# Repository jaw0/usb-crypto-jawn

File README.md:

Hardware encryption, sd card, and usb port.

The current firmware implements an encrypted
"usb stick".

Like [Bitlocker](http://css.csail.mit.edu/6.858/2013/readings/bitlocker.pdf),
but with the addition of per disk-block IVs + MACs.

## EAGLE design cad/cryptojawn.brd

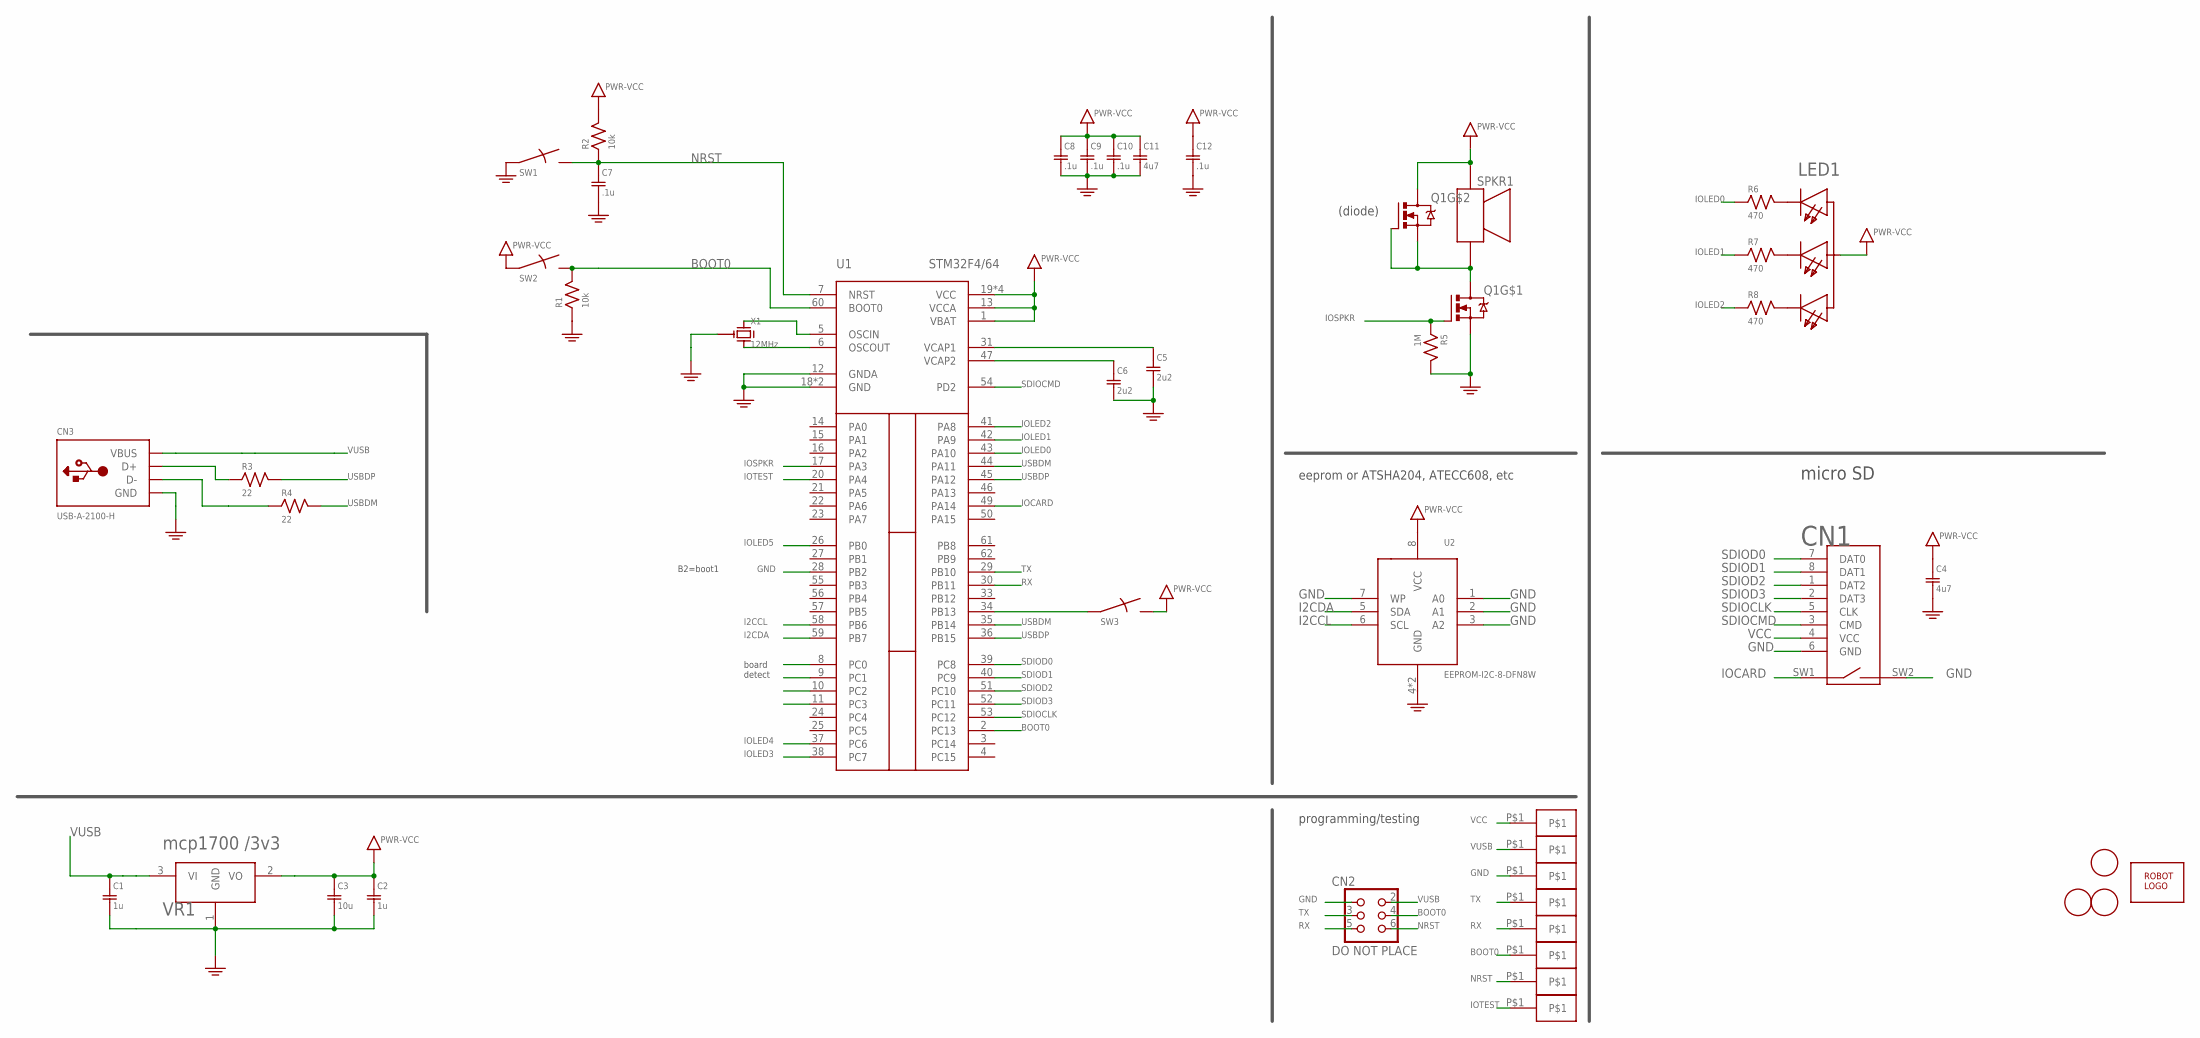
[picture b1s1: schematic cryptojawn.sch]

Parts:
C1, C2: 1u; SMD0603
C3: 10u; SMD0603
C4, C11: 4u7; SMD0603
C5, C6: 2u2; SMD0603
C7, C8, C9, C10, C12: .1u; SMD0603
CN1: MICROSDPLAIN; MICROSD/MOLEX/FRONT/PLAIN
CN2: DO NOT PLACE; HEADER-3X2-PTH1.27
CN3: USB-A-2100-H; MOLEX_480372100-HOLE
CN4, CN5, CN6, CN7, CN8, CN9, CN10, CN11: HEADER-1X1-SPOT; SPOT
LED1: LED-RGB-CA-PLCC4; PLCC4-3228
Q1: DMN63D8LDW; SC-70-6
R1, R2: 10k; SMD0603
R3, R4: 22; SMD0603
R5: 1M; SMD0603
R6, R7, R8: 470; SMD0603
SPKR1: SPKR-PUI-0440; PUI-0440
SW1, SW2, SW3: SWITCH-PTS810; PTS810
U1: STM32F4/64; TQFP64
U2: EEPROM-I2C-8-DFN8W; TDFN8EPW
U$1: ROBOTMAN-LOGO
U$2, U$3, U$4: FIDUCIAL; FIDUCIAL_1MM
VR1: mcp1700 /3v3; SOT-23-3@1
X1: 12MHz; RESONATOR-CSTCE

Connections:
BOOT0: CN2.4, CN8.P$1, R1.2, SW2.P$2, SW2.P$2B, U1.2 (PC13), U1.60 (BOOT0)
GND: C1.2, C2.2, C3.2, C4.2, C5.2, C6.2, C7.2, C8.2, C9.2, C10.2, C11.2, C12.2, CN1.6 (GND), CN1.SW2, CN2.1, CN3.4 (GND), CN3.P$1 (GND), CN3.P$2 (GND), CN5.P$1, Q1.1 (S), R1.1, R5.2, SW1.P$1, SW1.P$1B, U1.12 (GNDA), U1.18 (GND), U1.28 (PB2), U1.63 (GND), U2.1 (A0), U2.2 (A1), U2.3 (A2), U2.4 (GND), U2.7 (WP), U2.PAD (GND), VR1.1 (GND), X1.2 (G)
I2CCL: U1.58 (PB6), U2.6 (SCL)
I2CDA: U1.59 (PB7), U2.5 (SDA)
IOCARD: CN1.SW1, U1.49 (PA14)
IOLED0: R6.1, U1.43 (PA10)
IOLED1: R7.1, U1.42 (PA9)
IOLED2: R8.1, U1.41 (PA8)
IOLED3: U1.38 (PC7)
IOLED4: U1.37 (PC6)
IOLED5: U1.26 (PB0)
IOSPKR: Q1.2 (G), R5.1, U1.17 (PA3)
IOTEST: CN11.P$1, U1.20 (PA4)
unnamed: LED1.P$4 (CB), R7.2
unnamed: SW3.P$1, SW3.P$1B, U1.34 (PB13)
unnamed: LED1.P$2 (CR), R8.2
unnamed: C6.1, U1.47 (VCAP2)
unnamed: LED1.P$3 (CG), R6.2
unnamed: CN3.2 (D-), R4.1
unnamed: CN3.3 (D+), R3.1
unnamed: U1.5 (OSCIN), X1.1 (X1)
unnamed: U1.6 (OSCOUT), X1.3 (X2)
unnamed: Q1.4 (S), Q1.5 (G), Q1.6 (D), SPKR1.P$2 (P2)
unnamed: C5.1, U1.31 (VCAP1)
NRST: C7.1, CN2.6, CN9.P$1, R2.1, SW1.P$2, SW1.P$2B, U1.7 (NRST)
RX: CN2.5, CN7.P$1, U1.30 (PB11)
SDIOCLK: CN1.5 (CLK), U1.53 (PC12)
SDIOCMD: CN1.3 (CMD), U1.54 (PD2)
SDIOD0: CN1.7 (DAT0), U1.39 (PC8)
SDIOD1: CN1.8 (DAT1), U1.40 (PC9)
SDIOD2: CN1.1 (DAT2), U1.51 (PC10)
SDIOD3: CN1.2 (DAT3), U1.52 (PC11)
TX: CN2.3, CN6.P$1, U1.29 (PB10)
USBDM: R4.2, U1.35 (PB14), U1.44 (PA11)
USBDP: R3.2, U1.36 (PB15), U1.45 (PA12)
VCC: C2.1, C3.1, C4.1, C8.1, C9.1, C10.1, C11.1, C12.1, CN1.4 (VCC), CN10.P$1, LED1.P$1 (A), Q1.3 (D), R2.2, SPKR1.P$1 (P1), SW2.P$1, SW2.P$1B, SW3.P$2, SW3.P$2B, U1.1 (VBAT), U1.13 (VCCA), U1.19 (VCC), U1.32 (VCC), U1.48 (VCC), U1.64 (VCC), U2.8 (VCC), VR1.2 (VO)
VUSB: C1.1, CN2.2, CN3.1 (VBUS), CN4.P$1, VR1.3 (VI)

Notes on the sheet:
micro SD
eeprom or ATSHA204, ATECC608, etc
programming/testing
(diode)
B2=boot1
board detect

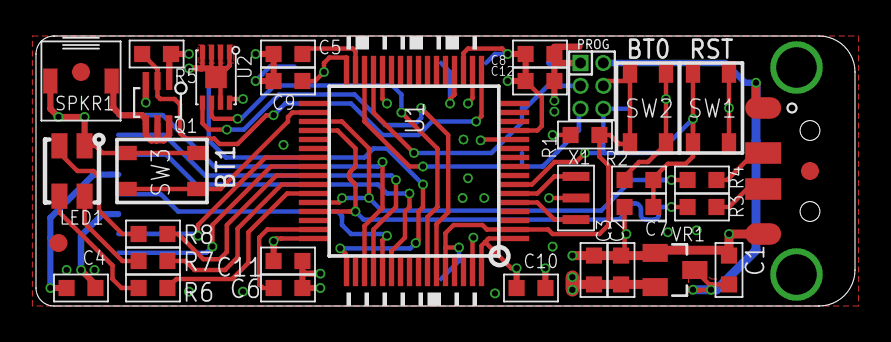
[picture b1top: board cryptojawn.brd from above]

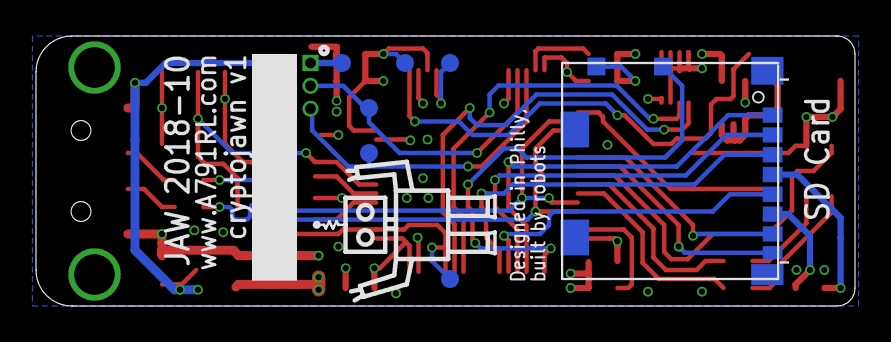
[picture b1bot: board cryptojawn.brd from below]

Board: 4 copper layers, 45.5 x 15.0 mm, 45 parts (10 on the bottom side), 34 nets.

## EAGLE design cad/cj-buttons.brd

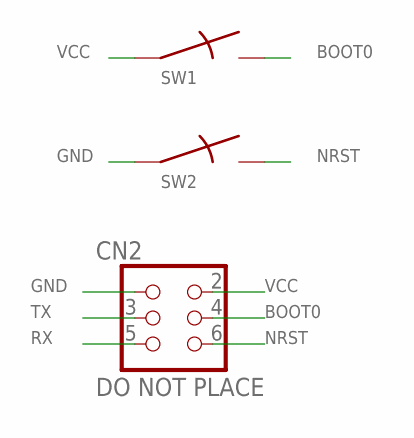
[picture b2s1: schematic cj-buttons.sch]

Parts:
CN2: DO NOT PLACE; HEADER-3X2-PTH1.27
SW1, SW2: SWITCHKMR211; KMR211

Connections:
BOOT0: CN2.4, SW1.2, SW1.4
GND: CN2.1, SW2.1, SW2.3
NRST: CN2.6, SW2.2, SW2.4
RX: CN2.5
TX: CN2.3
VCC: CN2.2, SW1.1, SW1.3

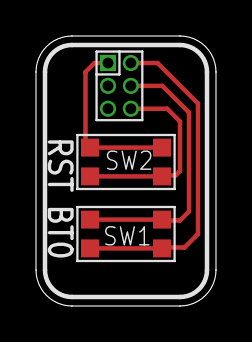
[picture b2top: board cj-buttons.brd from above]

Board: 2 copper layers, 10.0 x 15.0 mm, 3 parts (0 on the bottom side), 4 nets.

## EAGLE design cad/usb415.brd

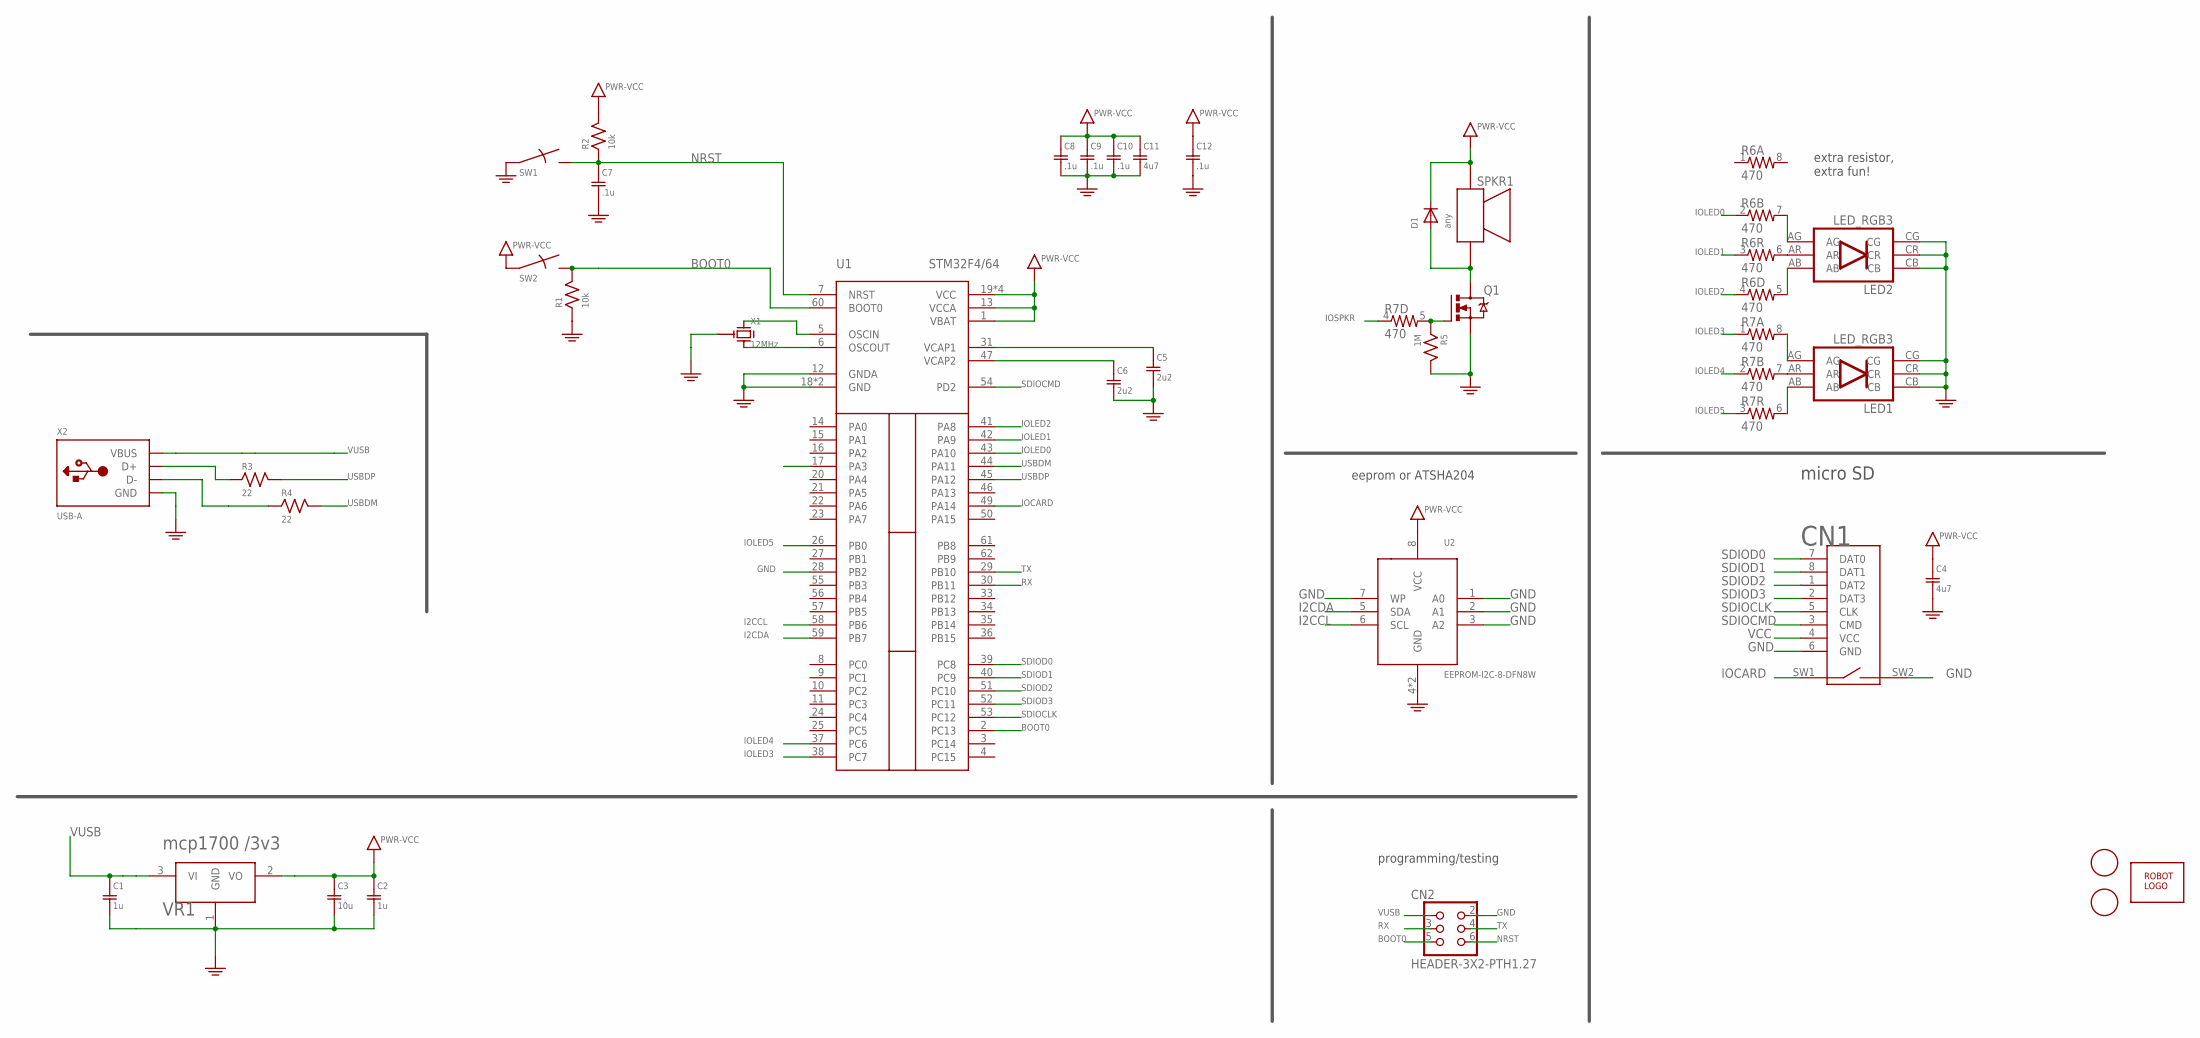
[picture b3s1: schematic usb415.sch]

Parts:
C1, C2: 1u; SMD0603
C3: 10u; SMD0603
C4, C11: 4u7; SMD0603
C5, C6: 2u2; SMD0603
C7, C8, C9, C10, C12: .1u; SMD0603
CN1: MICROSDPLAIN; MICROSD/MOLEX/FRONT/PLAIN
CN2: HEADER-3X2-PTH1.27
D1: any; SOD-323
LED1, LED2: LED_RGB3; SMDLEDRGB
Q1: IRLML6344TRPBF; SOT-23
R1, R2: 10k; SMD0603
R3, R4: 22; SMD0603
R5: 1M; SMD0603
R6, R7: 470; SMD-0603-ARV
SPKR1: SPKR-PUI-0440; PUI-0440
SW1, SW2: SWITCHKMR211; KMR211
U1: STM32F4/64; TQFP64
U2: EEPROM-I2C-8-DFN8W; TDFN8EPW
U$1: ROBOTMAN-LOGO
U$2, U$3: FIDUCIAL; FIDUCIAL_1MM
VR1: mcp1700 /3v3; SOT-23-3
X1: 12MHz; RESONATOR-CSTCE
X2: USB-A; MOLEX_480371000

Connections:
BOOT0: CN2.5, R1.2, SW2.2, SW2.4, U1.2 (PC13), U1.60 (BOOT0)
GND: C1.2, C2.2, C3.2, C4.2, C5.2, C6.2, C7.2, C8.2, C9.2, C10.2, C11.2, C12.2, CN1.6 (GND), CN1.SW2, CN2.2, LED1.CB, LED1.CG, LED1.CR, LED2.CB, LED2.CG, LED2.CR, Q1.2 (S), R1.1, R5.2, SW1.1, SW1.3, U1.12 (GNDA), U1.18 (GND), U1.28 (PB2), U1.63 (GND), U2.1 (A0), U2.2 (A1), U2.3 (A2), U2.4 (GND), U2.7 (WP), U2.PAD (GND), VR1.1 (GND), X1.2 (G), X2.4 (GND)
I2CCL: U1.58 (PB6), U2.6 (SCL)
I2CDA: U1.59 (PB7), U2.5 (SDA)
IOCARD: CN1.SW1, U1.49 (PA14)
IOLED0: R6.2 (1), U1.43 (PA10)
IOLED1: R6.3 (1), U1.42 (PA9)
IOLED2: R6.4 (1), U1.41 (PA8)
IOLED3: R7.1, U1.38 (PC7)
IOLED4: R7.2 (1), U1.37 (PC6)
IOLED5: R7.3 (1), U1.26 (PB0)
IOSPKR: R7.4 (1), U1.17 (PA3)
unnamed: LED1.AG, R7.8 (2)
unnamed: LED1.AR, R7.7 (2)
unnamed: LED1.AB, R7.6 (2)
unnamed: C6.1, U1.47 (VCAP2)
unnamed: LED2.AG, R6.7 (2)
unnamed: LED2.AR, R6.6 (2)
unnamed: R4.1, X2.2 (D-)
unnamed: R3.1, X2.3 (D+)
unnamed: Q1.1 (G), R5.1, R7.5 (2)
unnamed: LED2.AB, R6.5 (2)
unnamed: U1.5 (OSCIN), X1.1 (X1)
unnamed: U1.6 (OSCOUT), X1.3 (X2)
unnamed: D1.A, Q1.3 (D), SPKR1.P$2 (P2)
unnamed: C5.1, U1.31 (VCAP1)
NRST: C7.1, CN2.6, R2.1, SW1.2, SW1.4, U1.7 (NRST)
RX: CN2.3, U1.30 (PB11)
SDIOCLK: CN1.5 (CLK), U1.53 (PC12)
SDIOCMD: CN1.3 (CMD), U1.54 (PD2)
SDIOD0: CN1.7 (DAT0), U1.39 (PC8)
SDIOD1: CN1.8 (DAT1), U1.40 (PC9)
SDIOD2: CN1.1 (DAT2), U1.51 (PC10)
SDIOD3: CN1.2 (DAT3), U1.52 (PC11)
TX: CN2.4, U1.29 (PB10)
USBDM: R4.2, U1.44 (PA11)
USBDP: R3.2, U1.45 (PA12)
VCC: C2.1, C3.1, C4.1, C8.1, C9.1, C10.1, C11.1, C12.1, CN1.4 (VCC), D1.C, R2.2, SPKR1.P$1 (P1), SW2.1, SW2.3, U1.1 (VBAT), U1.13 (VCCA), U1.19 (VCC), U1.32 (VCC), U1.48 (VCC), U1.64 (VCC), U2.8 (VCC), VR1.2 (VO)
VUSB: C1.1, CN2.1, VR1.3 (VI), X2.1 (VBUS)

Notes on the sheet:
micro SD
eeprom or ATSHA204
extra resistor, extra fun!
programming/testing

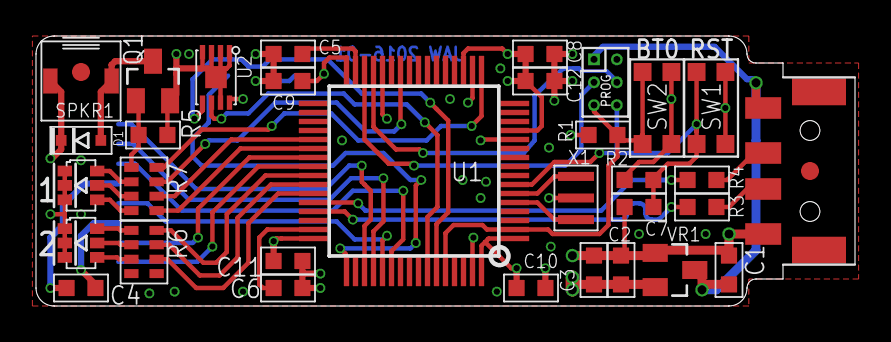
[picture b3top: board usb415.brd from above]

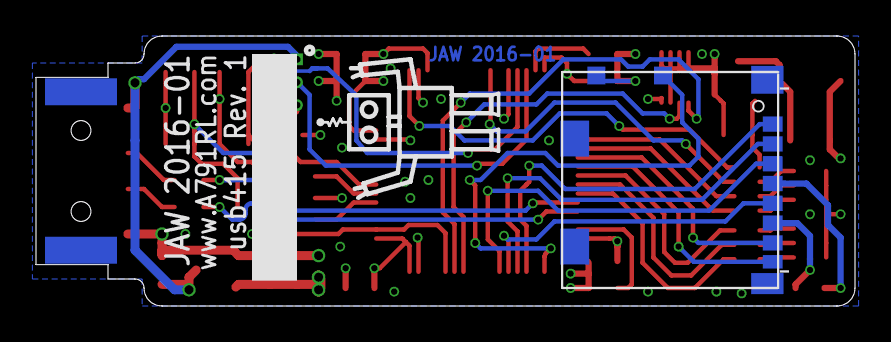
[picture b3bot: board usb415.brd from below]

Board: 4 copper layers, 45.5 x 15.0 mm, 36 parts (2 on the bottom side), 39 nets.

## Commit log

2015-12-11 2*rgb led, etc
2015-12-11 tweak
2015-12-12 R-array
2015-12-12 reverse polarity
2015-12-12 eeprom
2016-01-09 add gitignore
2016-01-09 add images
2016-01-15 sd connector
2016-01-21 add prog/test header
2018-09-08 seems to work
2018-09-08 rand
2018-09-09 elephant + entropy
2018-09-09 add firmware binary
2018-09-09 comments, etc
2018-10-01 rename file
2018-10-01 hardware rev.1
2018-10-04 add readme
2019-02-20 mini board
2019-02-20 misc
2019-02-20 unencrypted partition
